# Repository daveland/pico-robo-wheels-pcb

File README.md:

PCB in Kicad7 For pico-robo-wheels
RP 2040/ or Rp2350 compatible
This board will connecto to Either 100amp or 20 amp H-Bridge drivers On Ebay/aliexpress
It allows 2 motorized wheels in a differtial drive turning system
Each Wheel has a quadrature encoder to sense velocity and position
The cables to the encoders support 5V to the encoder , shifted to 3.3V via resistor dividers
OLD 0.9 inch display lets configuration , debug and control be performed
Rotry input encoder with switch for menu interaction
Estop input and Switch to stop all motion immediatly

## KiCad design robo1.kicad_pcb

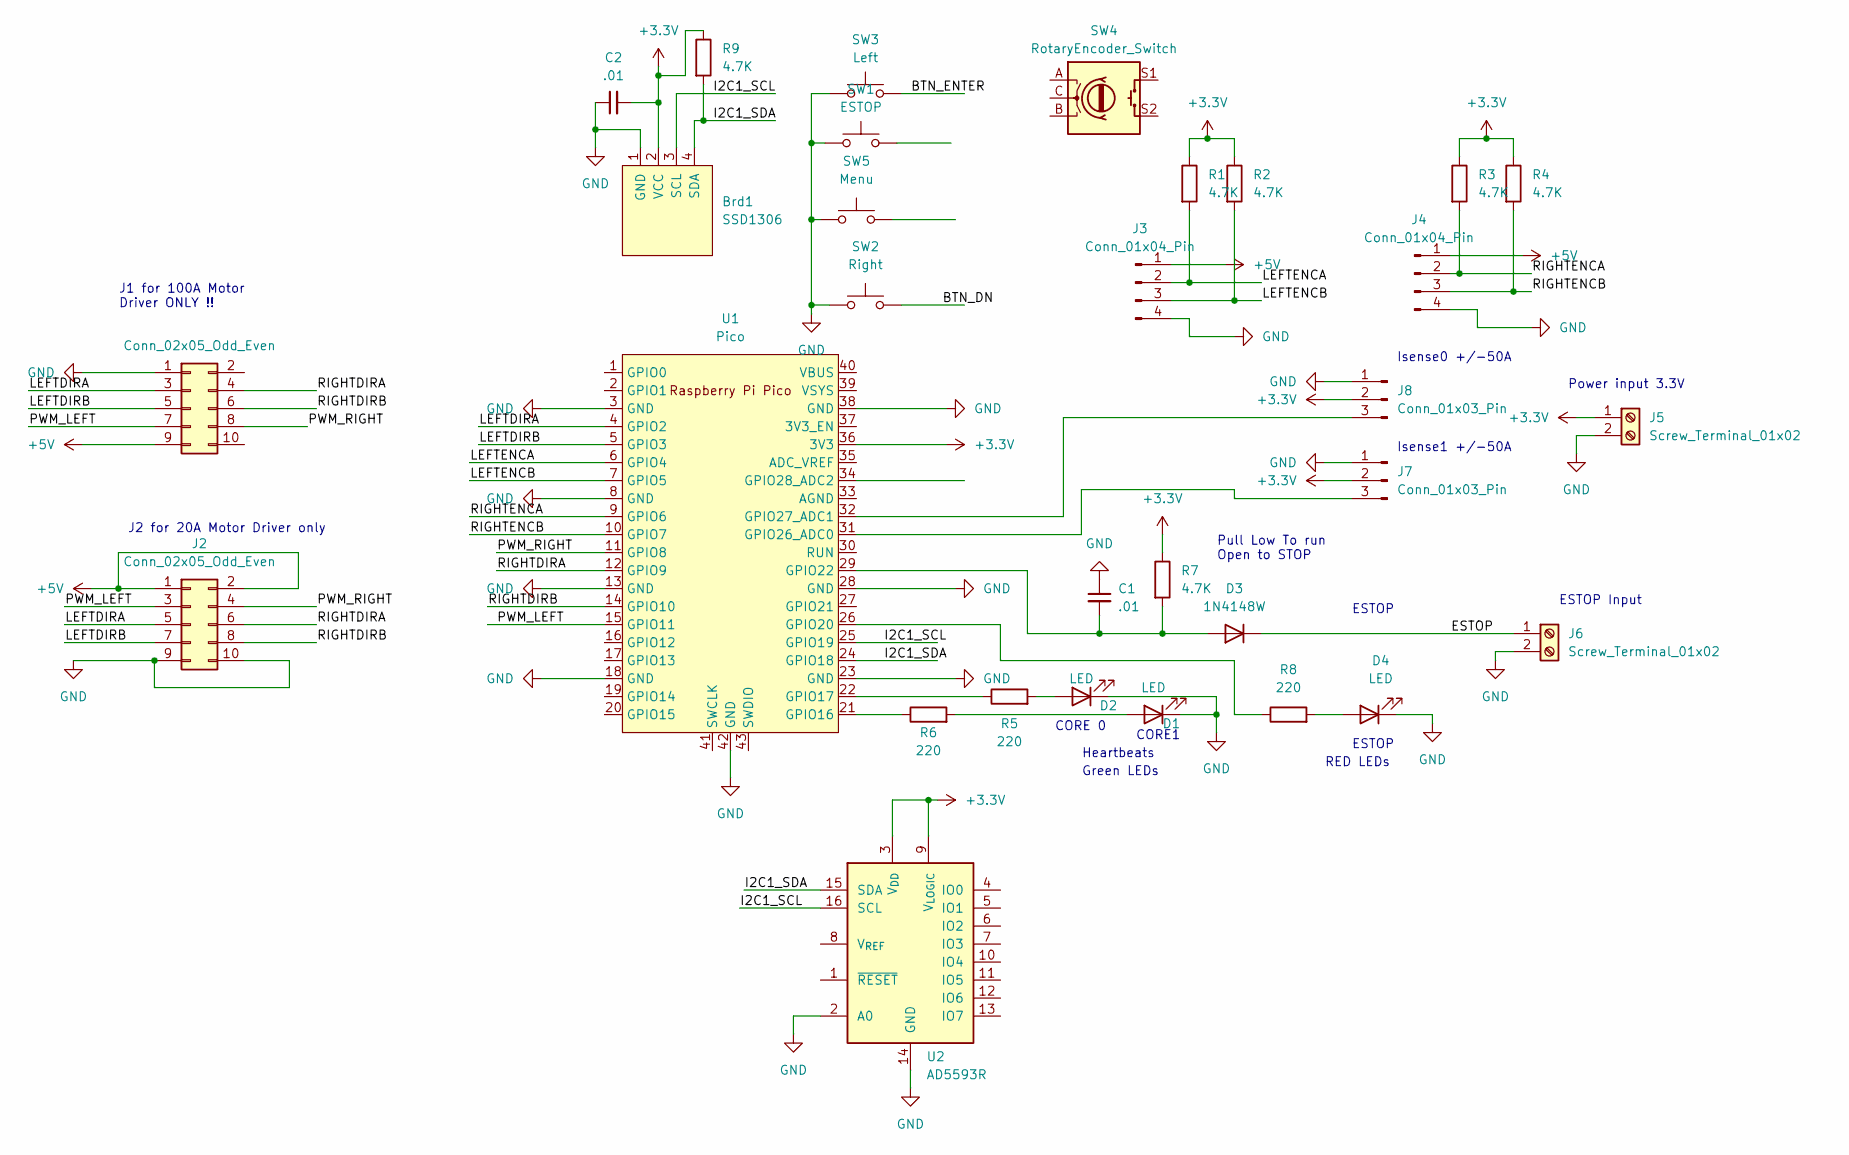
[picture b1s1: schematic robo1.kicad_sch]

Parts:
Brd1: SSD1306; 128x64OLED
C1, C2: .01; C_0603_1608Metric_Pad1.08x0.95mm_HandSolder
D1, D2, D4: LED; LED_1206_3216Metric_Pad1.42x1.75mm_HandSolder
D3: 1N4148W; D_SOD-123
J1, J2: Conn_02x05_Odd_Even; PinHeader_2x05_P2.54mm_Vertical
J3, J4: Conn_01x04_Pin; PinHeader_1x04_P2.54mm_Vertical
J5, J6: Screw_Terminal_01x02; TerminalBlock_bornier-2_P5.08mm
J7, J8: Conn_01x03_Pin; PinHeader_1x03_P2.54mm_Vertical
R1, R2, R3, R4, R7, R9: 4.7K; R_0201_0603Metric_Pad0.64x0.40mm_HandSolder
R5, R6, R8: 220; R_0201_0603Metric_Pad0.64x0.40mm_HandSolder
SW1: ESTOP; SW_PUSH_6mm
SW2: Right; SW_PUSH_6mm
SW3: Left; SW_PUSH_6mm
SW4: RotaryEncoder_Switch; RotaryEncoder_Alps_EC11E-Switch_Vertical_H20mm_CircularMoun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
SW5: Menu; SW_PUSH_6mm
U1: Pico; RPi_Pico_SMD_TH
U2: AD5593R; TSSOP-16_4.4x5mm_P0.65mm

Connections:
+3.3V: Brd1.2 (VCC), C2.2, J5.1, J7.2, J8.2, R1.1, R2.1, R3.1, R4.1, R7.1, R9.1, U1.36 (3V3), U2.3 (V_{DD}), U2.9 (V_{LOGIC})
+5V: J1.9, J2.1, J2.2, J3.1, J4.1
/BTN_DN: SW2.2
/BTN_ENTER: SW3.2
/ESTOP: D3.1 (K), J6.1
/I2C1_SCL: Brd1.3 (SCL), U1.25 (GPIO19), U2.16 (SCL)
/I2C1_SDA: Brd1.4 (SDA), R9.2, U1.24 (GPIO18), U2.15 (SDA)
/LEFTDIRA: J1.3, J2.5, U1.4 (GPIO2)
/LEFTDIRB: J1.5, J2.7, U1.5 (GPIO3)
/LEFTENCA: J3.2, R1.2, U1.6 (GPIO4)
/LEFTENCB: J3.3, R2.2, U1.7 (GPIO5)
/PWM_LEFT: J1.7, J2.3, U1.15 (GPIO11)
/PWM_RIGHT: J1.8, J2.4, U1.11 (GPIO8)
/RIGHTDIRA: J1.4, J2.6, U1.12 (GPIO9)
/RIGHTDIRB: J1.6, J2.8, U1.14 (GPIO10)
/RIGHTENCA: J4.2, R3.2, U1.9 (GPIO6)
/RIGHTENCB: J4.3, R4.2, U1.10 (GPIO7)
GND: Brd1.1 (GND), C1.1, C2.1, D1.1 (K), D2.1 (K), D4.1 (K), J1.1, J2.9, J2.10, J3.4, J4.4, J5.2, J6.2, J7.1, J8.1, SW1.1, SW2.1, SW3.1, SW5.1, U1.3 (GND), U1.8 (GND), U1.13 (GND), U1.18 (GND), U1.23 (GND), U1.28 (GND), U1.38 (GND), U1.42 (GND), U2.2 (A0), U2.14 (GND)
unnamed: D1.2 (A), R6.2
unnamed: D2.2 (A), R5.2
unnamed: C1.2, D3.2 (A), R7.2, U1.29 (GPIO22)
unnamed: D4.2 (A), R8.2
unnamed: J7.3, U1.31 (GPIO26_ADC0)
unnamed: J8.3, U1.32 (GPIO27_ADC1)
unnamed: R6.1, U1.21 (GPIO16)
unnamed: R5.1, U1.22 (GPIO17)
unnamed: R8.1, U1.26 (GPIO20)

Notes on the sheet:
ESTOP Input
J2 for 20A Motor Driver only
ESTOP
Isense0 +/-50A
Isense1 +/-50A
Heartbeats
Pull Low To run Open to STOP
Green LEDs
Power input 3.3V
J1 for 100A Motor Driver ONLY !!
CORE1
CORE 0
RED LEDs

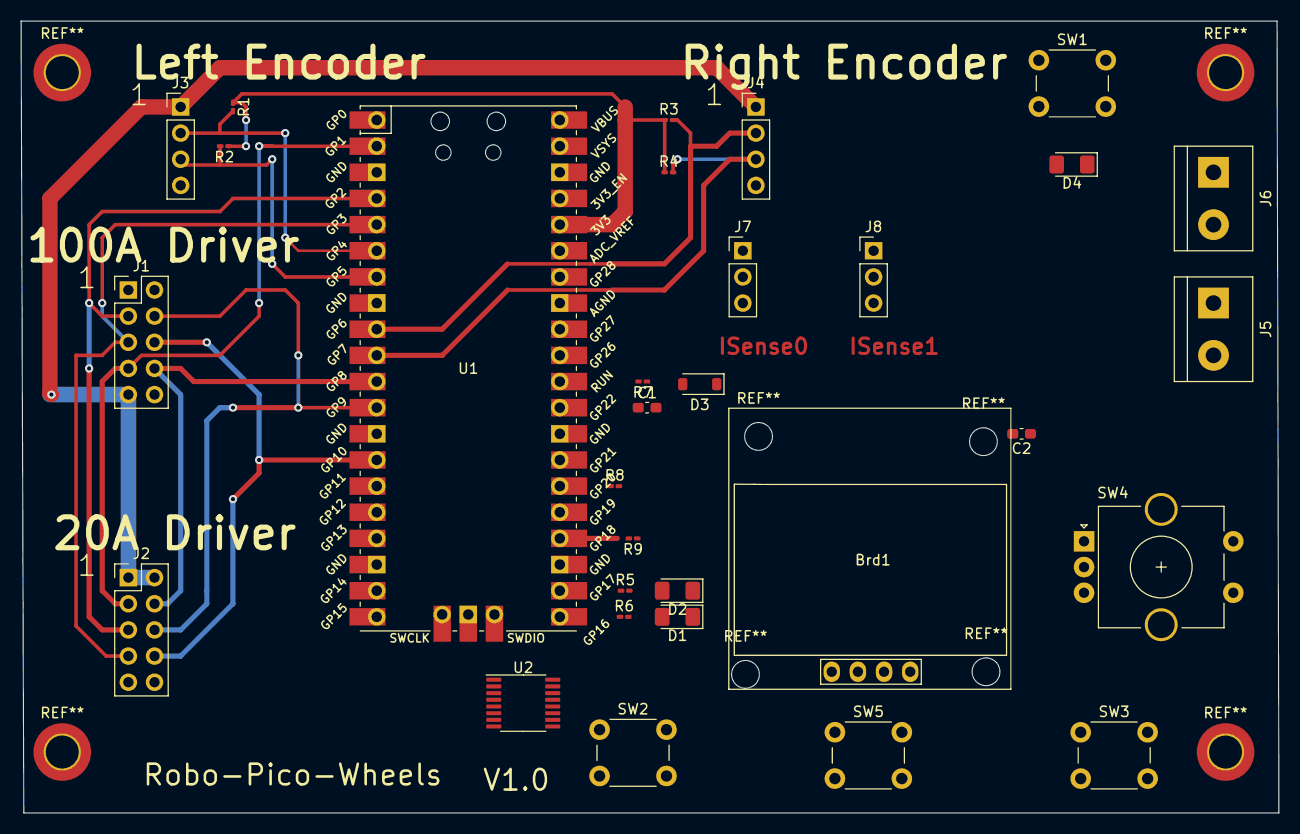
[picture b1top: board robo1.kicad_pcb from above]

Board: 2 copper layers, 122.2 x 76.9 mm, 31 parts (0 on the bottom side), 25 nets.

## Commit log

2024-11-10 update to use ad5590 and pb encoder
2024-12-13 add 5593 gpio
